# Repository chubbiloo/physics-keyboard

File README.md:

# physics-keyboard

A 33-key mechanical keyboard for writing physics and math.

[Main CAD](https://cad.onshape.com/documents/456d751678d0acb379dca94c/w/f9c0283b08451eaa8f4377e7/e/df621b50bfa725ee81dee17f?renderMode=0&uiState=6ae811c2d8704748218f6017)  
[Keycap CAD](https://www.tinkercad.com/things/8eVdOqgCMez-physics-keyboard-lettering)

## Features
- Greek letter input
- Math symbol input
- Left and right shift keys allow for 53 unique characters
- Caps Lock-like key allows switching between LaTeX and plain unicode output
- Compact square shape; similar in size to a large numpad/macropad

[BOM](bom.csv)

## Tools
- PCB design: KiCad, marbastlib
- CAD: OnShape
- Keycap lettering: Tinkercad
- Firmware: QMK

## Firmware
WinCompose is required for unicode input on Windows. For Mac or Linux, change UNICODE_SELECTED_MODES in config.h. Copy [this folder](firmware/physics_keyboard) into your keyboards directory after setting up QMK, then build and flash the firmware. [QMK docs](https://docs.qmk.fm/newbs_getting_started)

## Motivation
In our last years of high school, we wrote several lab reports in IB Physics which required us to input mathematical equations. We built this keyboard to make that process easier, in our classes in university.

## What we learned
Before this project, we wrote our formulae in the Google Docs equation editor. This project helped us learn LaTeX, a faster and more advanced tool than what we used previously. We also learned PCB design, including best practices for routing and design rule checking.

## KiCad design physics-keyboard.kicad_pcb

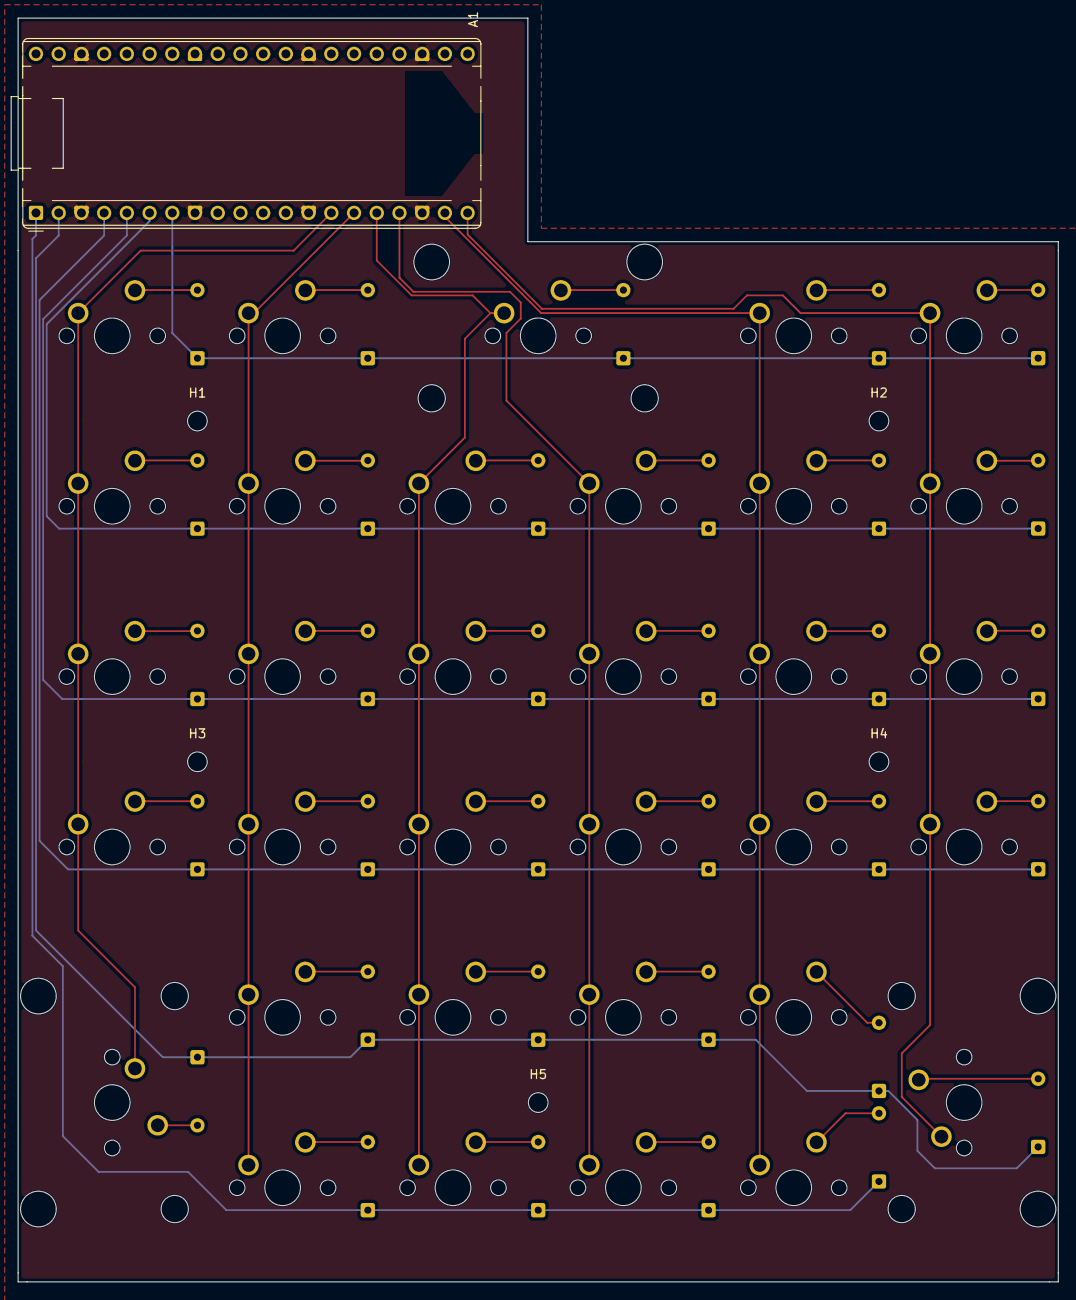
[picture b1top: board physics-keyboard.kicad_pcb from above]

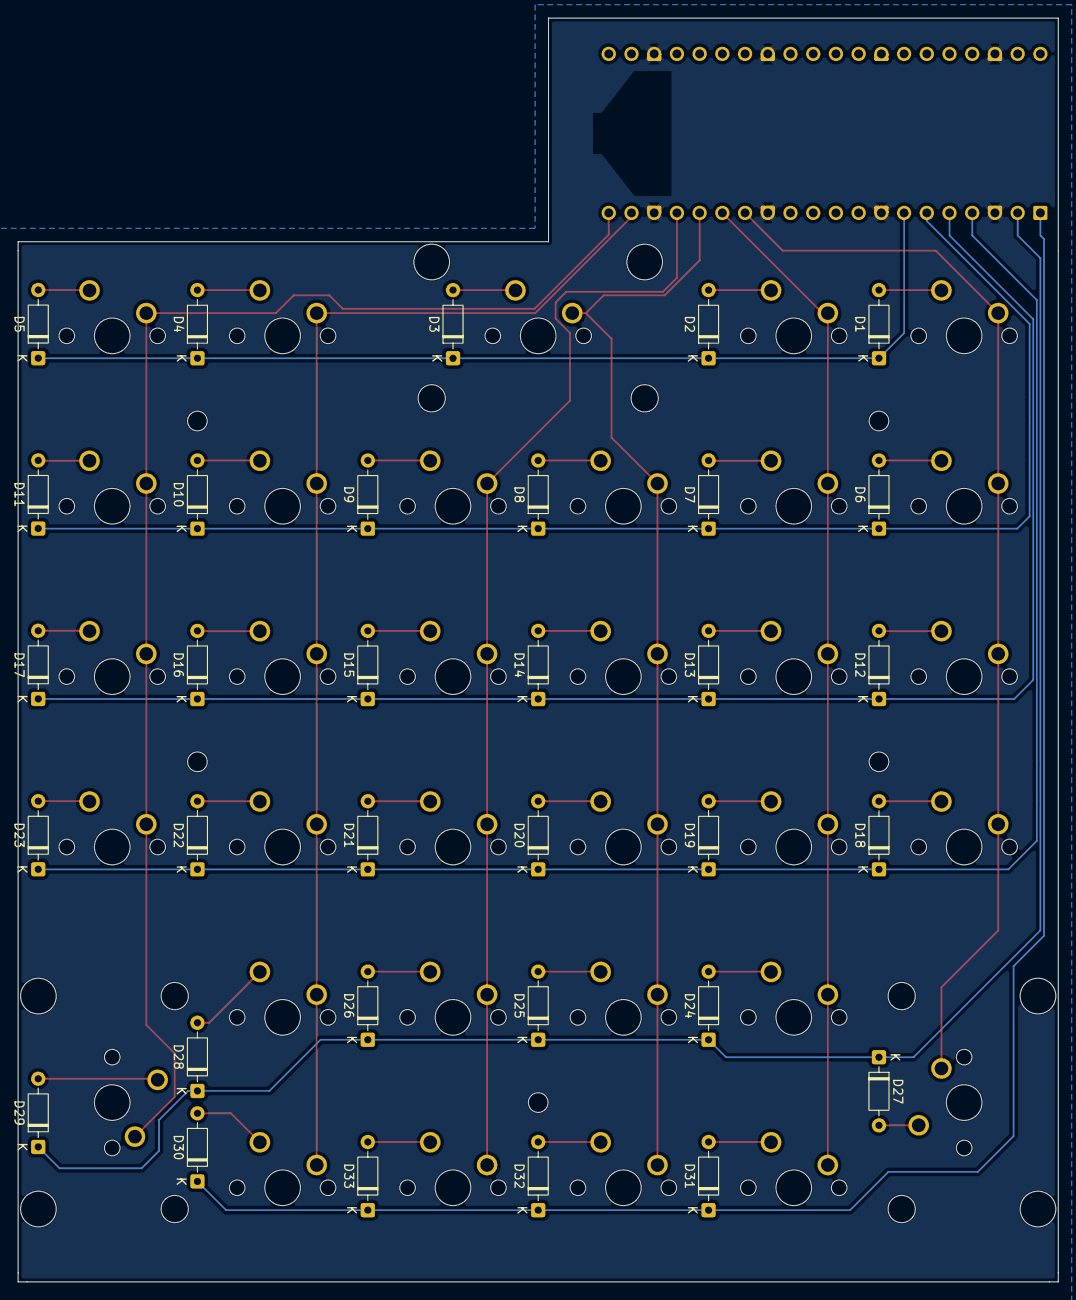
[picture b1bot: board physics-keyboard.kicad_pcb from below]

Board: 2 copper layers, 116.3 x 141.3 mm, 75 parts (33 on the bottom side), 46 nets.

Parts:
A1: RaspberryPi_Pico; RaspberryPi_Pico_Common_THT
D1, D2, D3, D4, D5, D6, D7, D8, D9, D10, D11, D12, D13, D14, D15, D16, D17, D18, D19, D20, D21, D22, D23, D24, D25, D26, D27, D28, D29, D30, D31, D32, D33: 1N4148; D_DO-35_SOD27_P7.62mm_Horizontal
H1, H2, H3, H4, H5: MountingHole; MountingHole_2.2mm_M2
S1, S2, S3: MX_stab; STAB_MX_2u
SW1, SW2, SW3, SW4, SW5, SW6, SW7, SW8, SW9, SW10, SW11, SW12, SW13, SW14, SW15, SW16, SW17, SW18, SW19, SW20, SW21, SW22, SW23, SW24, SW25, SW26, SW27, SW28, SW29, SW30, SW31, SW32, SW33: SW_Push; SW_MX_1u

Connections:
/COL0: A1.14 (GPIO10), SW1.1, SW6.1, SW12.1, SW18.1, SW28.1
/COL1: A1.15 (GPIO11), SW2.1, SW7.1, SW13.1, SW19.1, SW24.1, SW30.1
/COL2: A1.16 (GPIO12), SW3.1, SW8.1, SW14.1, SW20.1, SW25.1, SW31.1
/COL3: A1.17 (GPIO13), SW9.1, SW15.1, SW21.1, SW26.1, SW32.1
/COL4: A1.19 (GPIO14), SW4.1, SW10.1, SW16.1, SW22.1, SW27.1, SW33.1
/COL5: A1.20 (GPIO15), SW5.1, SW11.1, SW17.1, SW23.1, SW29.1
/ROW0: A1.7 (GPIO5), D1.1 (K), D2.1 (K), D3.1 (K), D4.1 (K), D5.1 (K)
/ROW1: A1.6 (GPIO4), D6.1 (K), D7.1 (K), D8.1 (K), D9.1 (K), D10.1 (K), D11.1 (K)
/ROW2: A1.5 (GPIO3), D12.1 (K), D13.1 (K), D14.1 (K), D15.1 (K), D16.1 (K), D17.1 (K)
/ROW3: A1.4 (GPIO2), D18.1 (K), D19.1 (K), D20.1 (K), D21.1 (K), D22.1 (K), D23.1 (K)
/ROW4: A1.2 (GPIO1), D24.1 (K), D25.1 (K), D26.1 (K), D27.1 (K), D28.1 (K), D29.1 (K)
/ROW5: A1.1 (GPIO0), D30.1 (K), D31.1 (K), D32.1 (K), D33.1 (K)
unnamed: A1.3 (GND), A1.8 (GND), A1.13 (GND), A1.18 (GND), A1.23 (GND), A1.28 (GND), A1.38 (GND)
unnamed: D1.2 (A), SW1.2
unnamed: D2.2 (A), SW2.2
unnamed: D6.2 (A), SW6.2
unnamed: D7.2 (A), SW7.2
unnamed: D12.2 (A), SW12.2
unnamed: D18.2 (A), SW18.2
unnamed: D8.2 (A), SW8.2
unnamed: D9.2 (A), SW9.2
unnamed: D10.2 (A), SW10.2
unnamed: D11.2 (A), SW11.2
unnamed: D13.2 (A), SW13.2
unnamed: D14.2 (A), SW14.2
unnamed: D15.2 (A), SW15.2
unnamed: D16.2 (A), SW16.2
unnamed: D17.2 (A), SW17.2
unnamed: D19.2 (A), SW19.2
unnamed: D20.2 (A), SW20.2
unnamed: D21.2 (A), SW21.2
unnamed: D22.2 (A), SW22.2
unnamed: D23.2 (A), SW23.2
unnamed: D24.2 (A), SW24.2
unnamed: D25.2 (A), SW25.2
unnamed: D26.2 (A), SW26.2
unnamed: D28.2 (A), SW27.2
unnamed: D3.2 (A), SW3.2
unnamed: D31.2 (A), SW30.2
unnamed: D32.2 (A), SW31.2
unnamed: D33.2 (A), SW32.2
unnamed: D30.2 (A), SW33.2
unnamed: D4.2 (A), SW4.2
unnamed: D27.2 (A), SW28.2
unnamed: D5.2 (A), SW5.2
unnamed: D29.2 (A), SW29.2
